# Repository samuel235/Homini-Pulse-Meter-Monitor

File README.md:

# Homini Pulse Meter Monitor

## Brief Description
This ATMEGA328P based board has been created to enable wireless monitoring of your power meter. The product comprises of two parts, one sensor attachment and one custom ATMEGA328P board that the sensor connects to. Both parts are enclosed inside of their own 3D printed enclosures to ensure safety to the devices.

This device has been designed to be located directly on your power meter, the sensor is stuck to the front and the controller is enclosed off to the side of the meter, designed to stick to the side also with Velcro, but you can put it where you wish. The sensor module is attached to the Controller device via a micro USB connector but obviously this can be modified to suit your personal needs.

There is a footprint to allow the use of a AT25DF512C Flash IC to allow the use of OTA updates with MYSBootloader, please refer to the MYSBootloader documentation for the use of this feature to discover the needed fuses and process to install MYSBootloader itself. This enables you the option of updating the device for future software updates without physically getting to the device. We have also allowed the use of a ATSHA204 hardware signing by including a footprint for the ATSHA204 IC on the controller board.

## Function
- To monitor power usage of your home and report back to controller software for a visible display of your consumed electricity.

## Physical Dimensions
- Sensor: 36mm x 24mm x 33mm (Width x Length x Height)
- Controller: TBA

## Connectors
- FTDI and SPI for firmware upgrades
- Micro USB for Powering the device
- Micro USB for sensor connection

## Connections
#### Radio Frequency
Footprints for the following radios will be included.
- nRF24L01 Radio Transceiver
- RFM69 Radio Transceiver

## Power Supply
##### Either of the following:
- Micro USB wall charger.
- CR2450 Coin-cell battery.

## Software
#### Bootloader
- Mains Powered: [Gertsanders' bootloader](https://www.mysensors.org/about/bootloader) running at 16MHz External crystal.
- Battery Powered: [Gertsanders' bootloader](https://www.mysensors.org/about/bootloader) running at 8MHz Internal or External crystal.

If you would like to use OTA updates then please use [MYSBootloader](https://www.mysensors.org/about/ota)

#### Sketch

Will update sketches once I receive PCBs to test different variants of software out:

[Generic pulse sensor sketch Located here](https://www.mysensors.org/build/pulse_power), alternatively you can find customised sketches on my [github](https://github.com/samuel235/Homini-Pulse-Meter-Monitor) inside of the relevant folder to your build type.

## Testing
Testing will commence once boards have been received and assembled.

1. Controller board - Mains powered version - **COMPLETED**
2. Sensor board - Mains powered version - **COMPLETED**

## TO-DO List
1. Add battery monitoring circuitry for next version

## Update Log:
- Micro-Controller board designed (25/03/17)
- Sensor board designed (15/03/17)
- Sensor board (battery) designed (06/04/17)
- All boards ordered using [PCBWay](www.pcbway.com) (10/04/17)
- Board arrived and testing commenced (26/04/17)

## Issues
1. No issues reported at current date.

## Appreciations
Special thanks to:
1. Scalz from the MySensors community that has provided relevant design files and circuit schematics to aid in this product design. [MySensors](https://forum.mysensors.org/user/scalz)/[github](https://github.com/scalz)
2. [Mysensors.org](Mysensors.org)
3. [Openhardware.org](Openhardware.org)
4. [Sparkfun](sparkfun.com) and [Adafruit](adafruit.com) for their parts library for Eagle

If you have any suggestions, please add to the forum post over at [MySensors forum post](https://forum.mysensors.org/topic/6460/homini-pulse-meter-monitor)

I'm very interested in all of your variations, improvements and applications of this module, please add them to the comments with pictures and/or Videos.

## Disclaimer
**_I do not advise you in any way to make/install this product into a property and therefore I take no responsibility for any issues, problems you have or even health implications that you endure while completing the installation or even using the product after installing. BUILD, USE and INSTALL AT YOUR OWN RISK_**

## Licensing
This product is licensed under the CC-BY-SA OpenHardware certificate. For more information please see https://creativecommons.org/licenses/by-sa/4.0/

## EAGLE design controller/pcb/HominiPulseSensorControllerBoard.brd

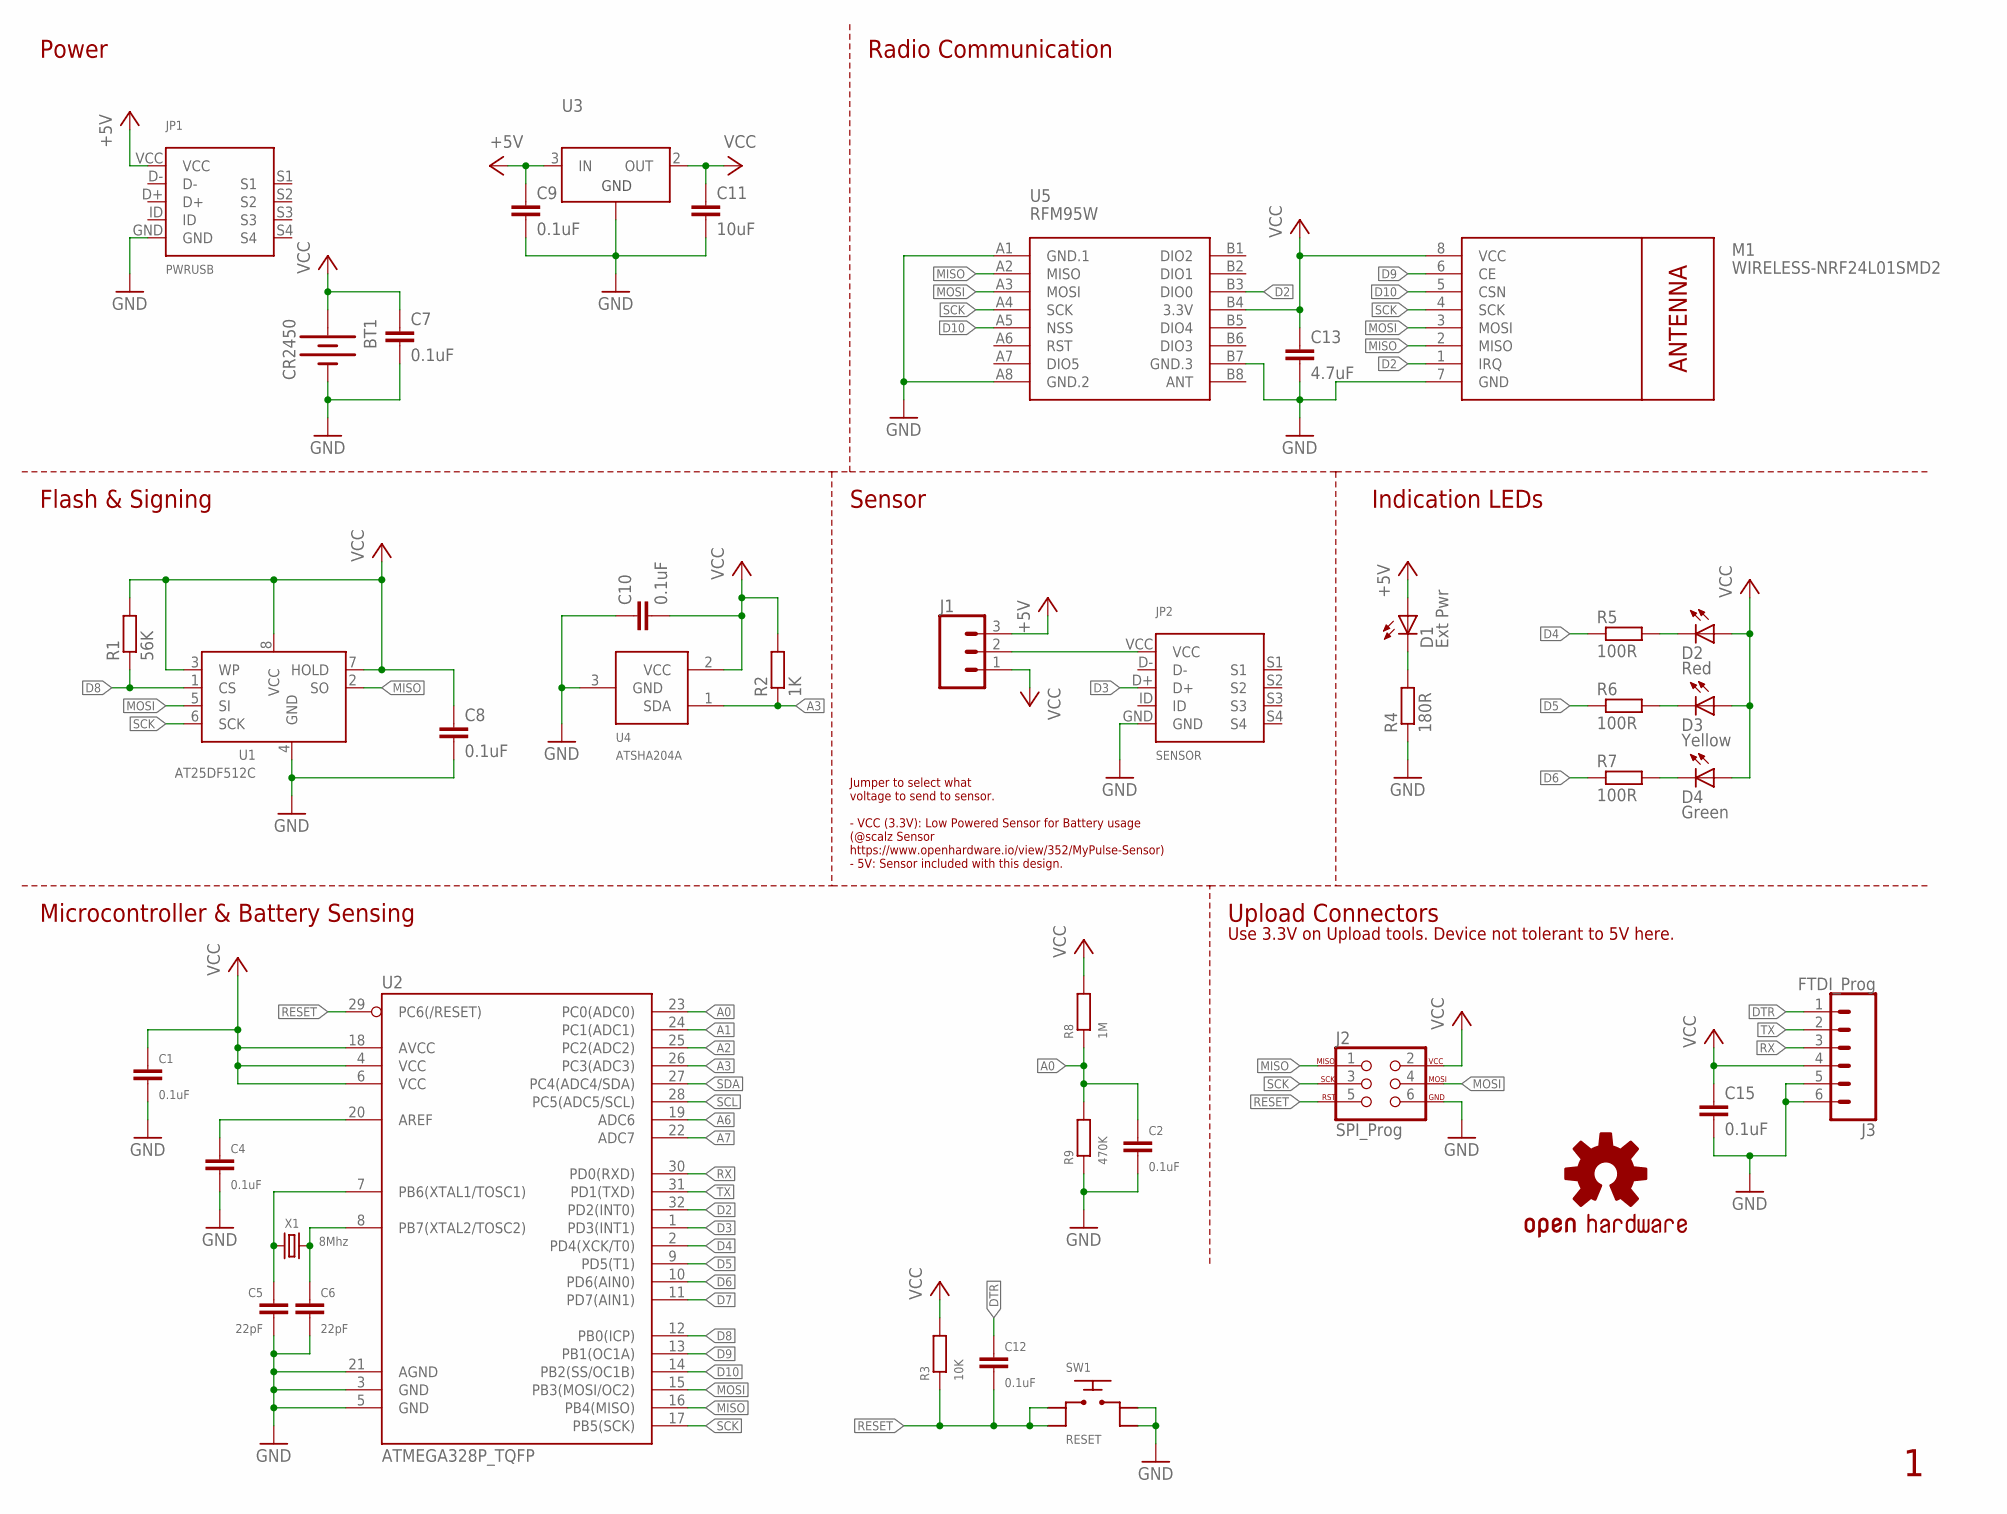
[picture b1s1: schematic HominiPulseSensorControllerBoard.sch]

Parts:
BT1: CR2450; BATTCON_24.5MM
C1, C2, C4, C7, C8, C9, C10, C12, C15: 0.1uF; C0603
C5, C6: 22pF; C0603
C11: 10uF; C0603
C13: 4.7uF; C0603
D1: Ext Pwr; LED3MM
D2: Red; LED3MM
D3: Yellow; LED3MM
D4: Green; LED3MM
J1: CONN_03; 1X03
J2: SPI_Prog; 2X3
J3: FTDI_Prog; 1X06_NO_SILK
JP1: PWRUSB; MICROUSBSMD
JP2: SENSOR; MICROUSBSMD
LOGO1: OSHW-LOGOM; OSHW-LOGO-M
M1: WIRELESS-NRF24L01SMD2; WIRELESS-NRF24L01-SMD-2
R1: 56K; R0603
R2: 1K; R0603
R3: 10K; R0603
R4: 180R; R0603
R5, R6, R7: 100R; R0603
R8: 1M; R0603
R9: 470K; R0603
SW1: RESET; SMD5X5X1.5MM
U1: AT25DF512C; SOIC-8
U2: ATMEGA328P_TQFP; TQFP32-08
U3: LD1117V33; SOC-223
U4: ATSHA204A; SOT23
U5: RFM95W; WIRELESS-LORA-RFM95W#SMD
X1: 8Mhz; HC-49S-SMT

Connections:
+5V: C9.1, D1.A, J1.3, JP1.VCC, U3.3 (IN)
A0: C2.1, R8.1, R9.2, U2.23 (PC0(ADC0))
A1: U2.24 (PC1(ADC1))
A2: U2.25 (PC2(ADC2))
A3: R2.1, U2.26 (PC3(ADC3)), U4.1 (SDA)
A6: U2.19 (ADC6)
A7: U2.22 (ADC7)
D2: M1.1 (IRQ), U2.32 (PD2(INT0)), U5.B3 (DIO0)
D3: JP2.D+, U2.1 (PD3(INT1))
D4: R5.1, U2.2 (PD4(XCK/T0))
D5: R6.1, U2.9 (PD5(T1))
D6: R7.1, U2.10 (PD6(AIN0))
D7: U2.11 (PD7(AIN1))
D8: R1.1, U1.1 (CS), U2.12 (PB0(ICP))
D9: M1.6 (CE), U2.13 (PB1(OC1A))
D10: M1.5 (CSN), U2.14 (PB2(SS/OC1B)), U5.A5 (NSS)
DTR: C12.1, J3.1
GND: BT1.2 (-), C1.2, C2.2, C4.2, C5.2, C6.2, C7.2, C8.2, C9.2, C10.1, C11.2, C13.2, C15.2, J2.6, J3.5, J3.6, JP1.GND, JP2.GND, M1.7 (GND), R4.1, R9.1, SW1.3, SW1.4, U1.4 (GND), U2.3 (GND), U2.5 (GND), U2.21 (AGND), U3.1 (GND), U4.3 (GND), U5.A1 (GND.1), U5.A8 (GND.2), U5.B7 (GND.3)
MISO: J2.1, M1.2 (MISO), U1.2 (SO), U2.16 (PB4(MISO)), U5.A2 (MISO)
MOSI: J2.4, M1.3 (MOSI), U1.5 (SI), U2.15 (PB3(MOSI/OC2)), U5.A3 (MOSI)
unnamed: C6.1, U2.8 (PB7(XTAL2/TOSC2)), X1.1
unnamed: C5.1, U2.7 (PB6(XTAL1/TOSC1)), X1.2
unnamed: C4.1, U2.20 (AREF)
unnamed: J1.2, JP2.VCC
unnamed: D1.K (C), R4.2
unnamed: D2.K (C), R5.2
unnamed: D3.K (C), R6.2
unnamed: D4.K (C), R7.2
RESET: C12.2, J2.5, R3.1, SW1.1, SW1.2, U2.29 (PC6(/RESET))
RX: J3.3, U2.30 (PD0(RXD))
SCK: J2.3, M1.4 (SCK), U1.6 (SCK), U2.17 (PB5(SCK)), U5.A4 (SCK)
SCL: U2.28 (PC5(ADC5/SCL))
SDA: U2.27 (PC4(ADC4/SDA))
TX: J3.2, U2.31 (PD1(TXD))
VCC: BT1.1 (+), C1.1, C7.1, C8.1, C10.2, C11.1, C13.1, C15.1, D2.A, D3.A, D4.A, J1.1, J2.2, J3.4, M1.8 (VCC), R1.2, R2.2, R3.2, R8.2, U1.3 (WP), U1.7 (HOLD), U1.8 (VCC), U2.4 (VCC), U2.6 (VCC), U2.18 (AVCC), U3.2 (OUT), U4.2 (VCC), U5.B4 (3.3V)

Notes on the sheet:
Jumper to select what voltage to send to sensor. - VCC (3.3V): Low Powered Sensor for Battery usage (@scalz Sensor https://www.openhardware.io/view/352/MyPulse-Sensor) - 5V: Sensor included with this design.
Upload Connectors
Microcontroller & Battery Sensing
Power
Flash & Signing
Sensor
Indication LEDs
Radio Communication
Use 3.3V on Upload tools. Device not tolerant to 5V here.

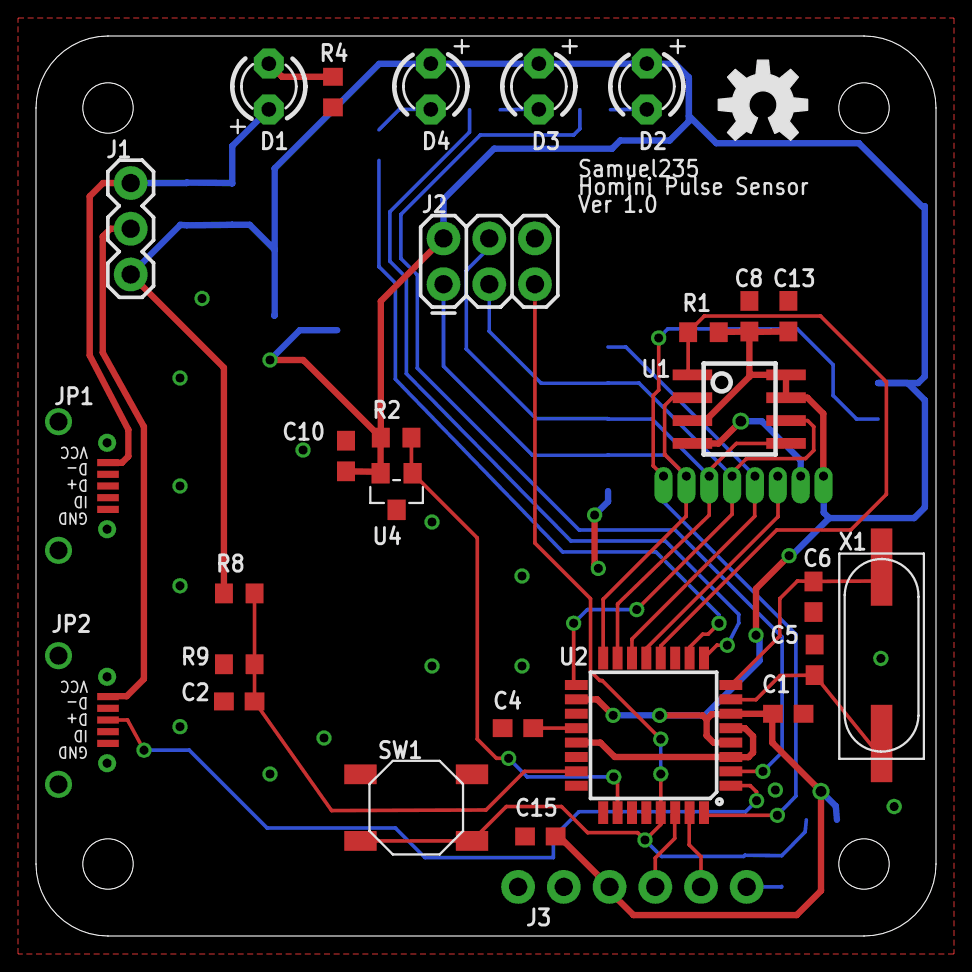
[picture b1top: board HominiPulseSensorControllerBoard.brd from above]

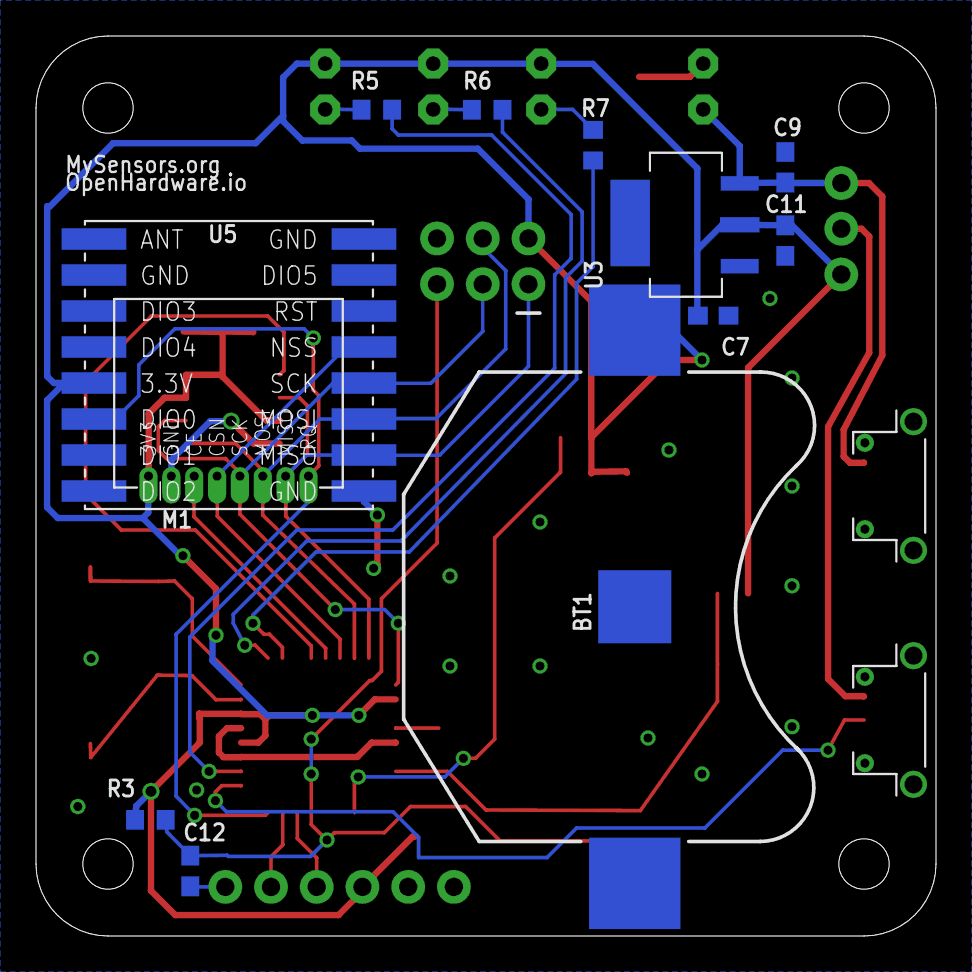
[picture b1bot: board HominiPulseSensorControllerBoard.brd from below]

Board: 2 copper layers, 50.0 x 50.0 mm, 41 parts (12 on the bottom side), 28 nets.

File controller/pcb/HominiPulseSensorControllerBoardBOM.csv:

"Part";"Value";"Device";"Package";"Description";"PROD_ID";"VALUE";
"BT1";"CR2450";"CR2450";"BATTCON_24.5MM";"";"";"";
"C1";"0.1uF";"C-EUC0603";"C0603";"CAPACITOR, European symbol";"";"";
"C2";"0.1uF";"C-EUC0603";"C0603";"CAPACITOR, European symbol";"";"";
"C4";"0.1uF";"C-EUC0603";"C0603";"CAPACITOR, European symbol";"";"";
"C5";"22pF";"C-EUC0603";"C0603";"CAPACITOR, European symbol";"";"";
"C6";"22pF";"C-EUC0603";"C0603";"CAPACITOR, European symbol";"";"";
"C7";"0.1uF";"C-EUC0603";"C0603";"CAPACITOR, European symbol";"";"";
"C8";"0.1uF";"C-EUC0603";"C0603";"CAPACITOR, European symbol";"";"";
"C9";"0.1uF";"C-EUC0603";"C0603";"CAPACITOR, European symbol";"";"";
"C10";"0.1uF";"C-EUC0603";"C0603";"CAPACITOR, European symbol";"";"";
"C11";"10uF";"C-EUC0603";"C0603";"CAPACITOR, European symbol";"";"";
"C12";"0.1uF";"C-EUC0603";"C0603";"CAPACITOR, European symbol";"";"";
"C13";"4.7uF";"C-EUC0603";"C0603";"CAPACITOR, European symbol";"";"";
"C15";"0.1uF";"C-EUC0603";"C0603";"CAPACITOR, European symbol";"";"";
"D1";"Ext Pwr";"LED3MM";"LED3MM";"LED";"";"";
"D2";"Red";"LED3MM";"LED3MM";"LED";"";"";
"D3";"Yellow";"LED3MM";"LED3MM";"LED";"";"";
"D4";"Green";"LED3MM";"LED3MM";"LED";"";"";
"J1";"";"CONN_03";"1X03";"Multi connection point. Often used as Generic Header-pin footprint for 0.1 inch spaced/style header connections";"";"";
"J2";"SPI_Prog";"AVR_SPI_PROG_3X2PTH";"2X3";"AVR ISP 6 Pin";"";"";
"J3";"FTDI_Prog";"CONN_06NO_SILK_FEMALE_PTH";"1X06_NO_SILK";"Multi connection point. Often used as Generic Header-pin footprint for 0.1 inch spaced/style header connections";"CONN-08437";"";
"JP1";"PWRUSB";"MICROUSBSMD";"MICROUSBSMD";"";"";"";
"JP2";"SENSOR";"MICROUSBSMD";"MICROUSBSMD";"";"";"";
"M1";"WIRELESS-NRF24L01SMD2";"WIRELESS-NRF24L01SMD2";"WIRELESS-NRF24L01-SMD-2";"2.4 GHz Wireless Module based on NRF24L01 chip";"";"";
"R1";"56K";"R-EU_R0603";"R0603";"RESISTOR, European symbol";"";"";
"R2";"1K";"R-EU_R0603";"R0603";"RESISTOR, European symbol";"";"";
"R3";"10K";"R-EU_R0603";"R0603";"RESISTOR, European symbol";"";"";
"R4";"180R";"R-EU_R0603";"R0603";"RESISTOR, European symbol";"";"";
"R5";"100R";"R-EU_R0603";"R0603";"RESISTOR, European symbol";"";"";
"R6";"100R";"R-EU_R0603";"R0603";"RESISTOR, European symbol";"";"";
"R7";"100R";"R-EU_R0603";"R0603";"RESISTOR, European symbol";"";"";
"R8";"1M";"R-EU_R0603";"R0603";"RESISTOR, European symbol";"";"";
"R9";"470K";"R-EU_R0603";"R0603";"RESISTOR, European symbol";"";"";
"SW1";"RESET";"SMD5X5X1.5MM";"SMD5X5X1.5MM";"";"";"";
"U1";"AT25DF512C";"AT25DF512C";"SOIC-8";"";"";"";
"U2";"ATMEGA328P_TQFP";"ATMEGA328P_TQFP";"TQFP32-08";"Popular 328P in QFP";"IC-09069";"ATMEGA328P_TQFP";
"U3";"";"LD1117V33";"SOC-223";"";"";"";
"U4";"ATSHA204A";"ATSHA204A";"SOT23";"";"";"";
"U5";"RFM95W";"WIRELESS-LORA-RFM95W#SMD";"WIRELESS-LORA-RFM95W#SMD";"868/915 MHz LoRa Radio Transceiver Module based on SX1276 chip";"";"";
"X1";"8Mhz";"HC-49S-SMT";"HC-49S-SMT";"";"";"";

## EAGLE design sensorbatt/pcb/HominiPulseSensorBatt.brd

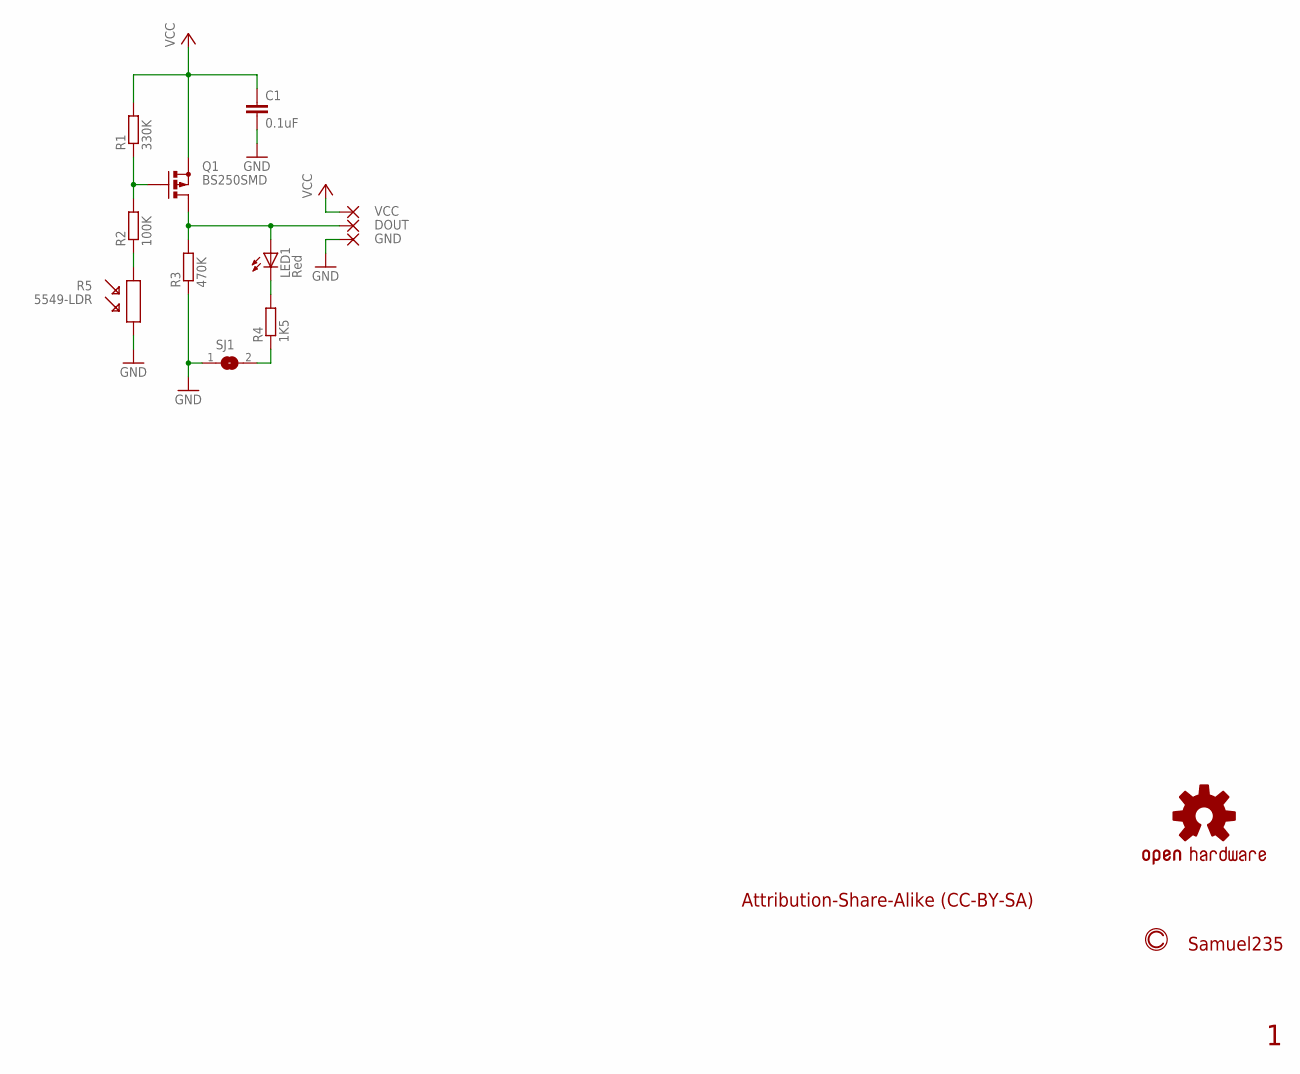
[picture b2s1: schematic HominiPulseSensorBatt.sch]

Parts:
C1: 0.1uF; C0603
DOUT: SMD2; SMD1,27-2,54
GND: SMD2; SMD1,27-2,54
LED1: Red; LED3MM
LOGO1: OSHW-LOGOS; OSHW-LOGO-S
Q1: BS250SMD; SOT23
R1: 330K; R0603
R2: 100K; R0603
R3: 470K; R0603
R4: 1K5; R0603
R5: 5549-LDR; LDR-PTH
SJ1: SJ
VCC: SMD2; SMD1,27-2,54

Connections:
GND: C1.2, GND.1, R3.1, R5.1, SJ1.1
unnamed: Q1.1 (G), R1.1, R2.2
unnamed: R2.1, R5.2
unnamed: DOUT.1, LED1.A, Q1.3 (D), R3.2
unnamed: R4.1, SJ1.2
unnamed: LED1.K (C), R4.2
VCC: C1.1, Q1.2 (S), R1.2, VCC.1

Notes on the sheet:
Samuel235
Attribution-Share-Alike (CC-BY-SA)

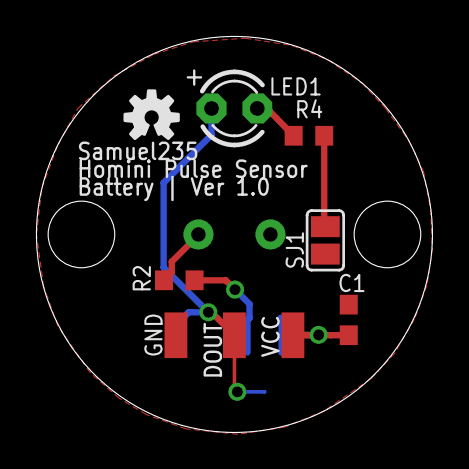
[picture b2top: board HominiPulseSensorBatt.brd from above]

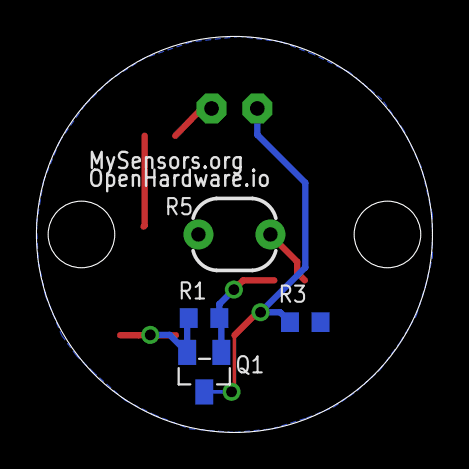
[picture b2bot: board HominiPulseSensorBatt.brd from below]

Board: 2 copper layers, 22.0 x 22.0 mm, 13 parts (4 on the bottom side), 7 nets.

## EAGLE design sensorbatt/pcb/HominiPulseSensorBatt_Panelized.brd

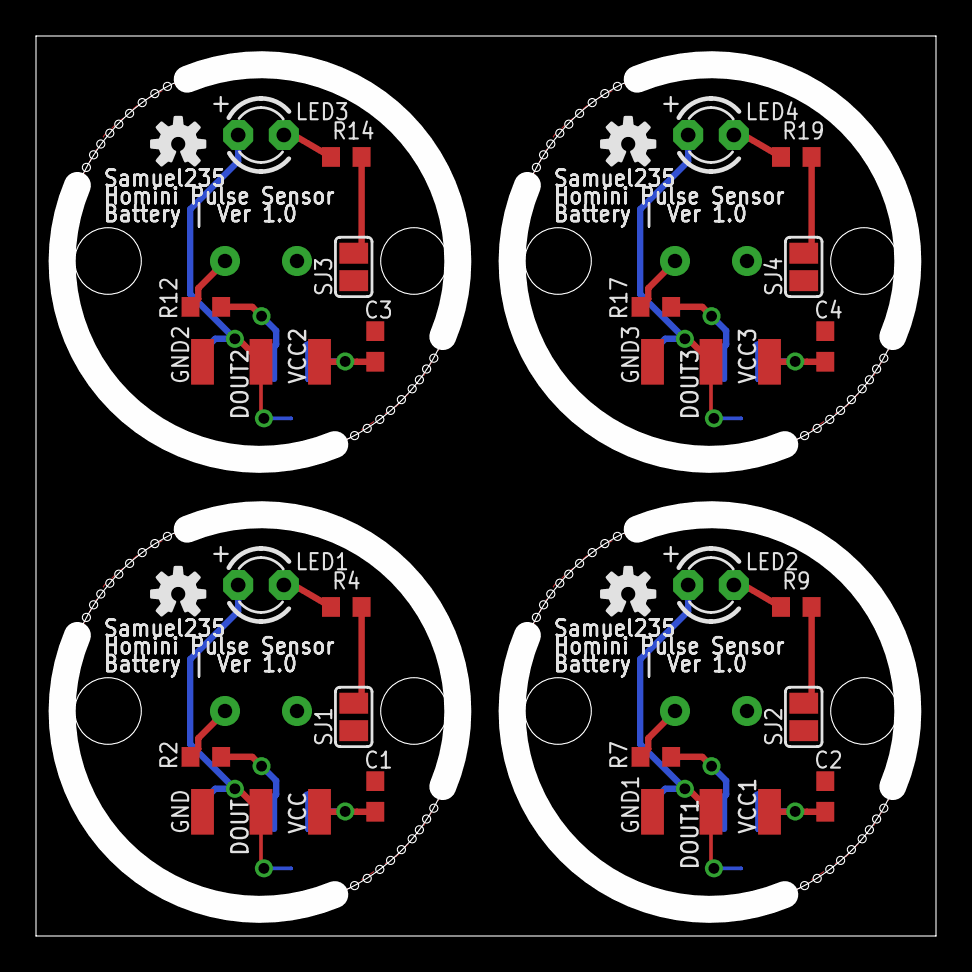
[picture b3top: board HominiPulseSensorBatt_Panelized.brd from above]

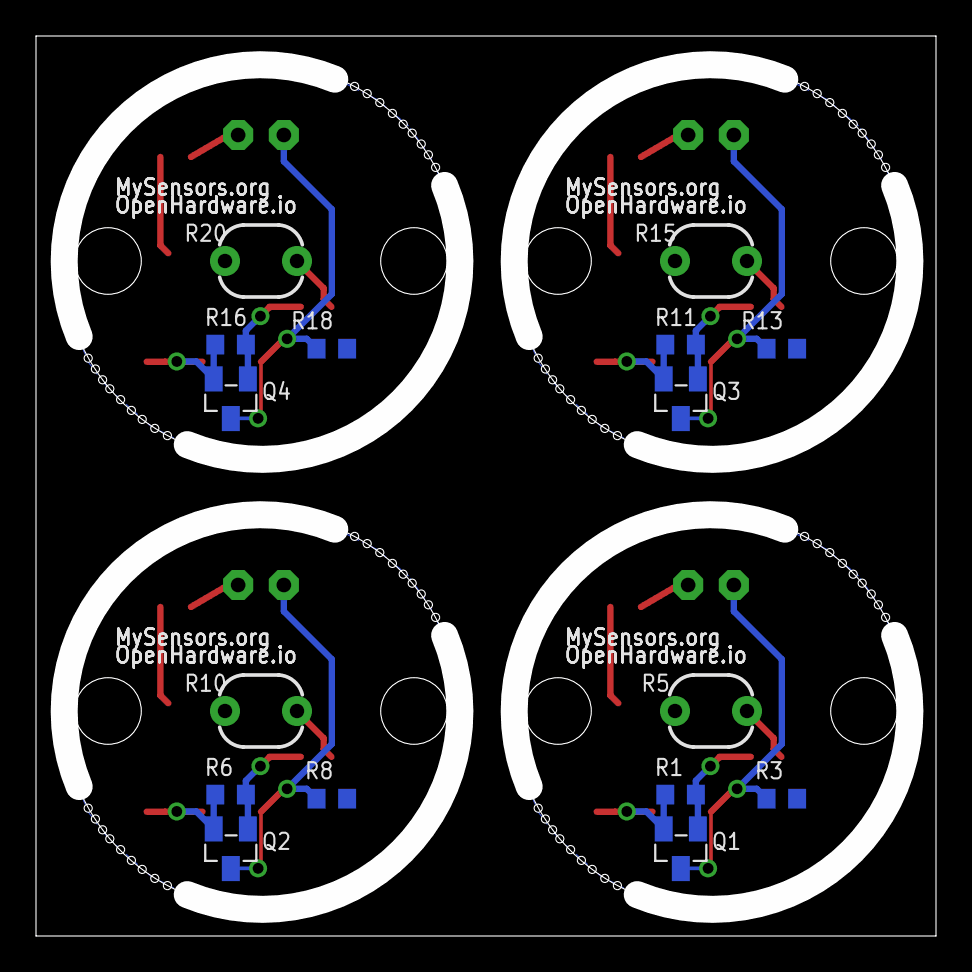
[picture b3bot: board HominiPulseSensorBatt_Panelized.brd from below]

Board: 2 copper layers, 48.5 x 48.5 mm, 52 parts (16 on the bottom side), 28 nets.

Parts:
C1, C2, C3, C4: 0.1uF; C0603
DOUT, DOUT1, DOUT2, DOUT3: SMD1,27-2,54
GND, GND1, GND2, GND3: SMD1,27-2,54
LED1, LED2, LED3, LED4: Red; LED3MM
LOGO1, LOGO2, LOGO3, LOGO4: OSHW-LOGOS; OSHW-LOGO-S
Q1, Q2, Q3, Q4: BS250SMD; SOT23
R1, R6, R11, R16: 330K; R0603
R2, R7, R12, R17: 100K; R0603
R3, R8, R13, R18: 470K; R0603
R4, R9, R14, R19: 1K5; R0603
R5, R10, R15, R20: 5549-LDR; LDR-PTH
SJ1, SJ2, SJ3, SJ4: SJ
VCC, VCC1, VCC2, VCC3: SMD1,27-2,54

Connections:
GND: C1.2, GND.1, R3.1, R5.1, SJ1.1
GND1: C2.2, GND1.1, R8.1, R10.1, SJ2.1
GND2: C3.2, GND2.1, R13.1, R15.1, SJ3.1
GND3: C4.2, GND3.1, R18.1, R20.1, SJ4.1
unnamed: Q1.1, R1.1, R2.2
unnamed: R2.1, R5.2
unnamed: DOUT.1, LED1.A, Q1.3, R3.2
unnamed: R4.1, SJ1.2
unnamed: LED1.K, R4.2
unnamed: Q2.1, R6.1, R7.2
unnamed: R7.1, R10.2
unnamed: DOUT1.1, LED2.A, Q2.3, R8.2
unnamed: R9.1, SJ2.2
unnamed: LED2.K, R9.2
unnamed: Q3.1, R11.1, R12.2
unnamed: R12.1, R15.2
unnamed: DOUT2.1, LED3.A, Q3.3, R13.2
unnamed: R14.1, SJ3.2
unnamed: LED3.K, R14.2
unnamed: Q4.1, R16.1, R17.2
unnamed: R17.1, R20.2
unnamed: DOUT3.1, LED4.A, Q4.3, R18.2
unnamed: R19.1, SJ4.2
unnamed: LED4.K, R19.2
VCC: C1.1, Q1.2, R1.2, VCC.1
VCC1: C2.1, Q2.2, R6.2, VCC1.1
VCC2: C3.1, Q3.2, R11.2, VCC2.1
VCC3: C4.1, Q4.2, R16.2, VCC3.1

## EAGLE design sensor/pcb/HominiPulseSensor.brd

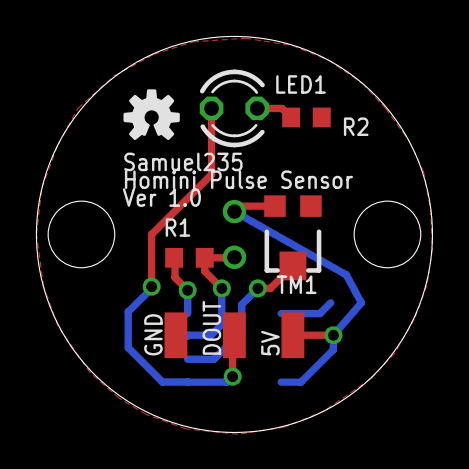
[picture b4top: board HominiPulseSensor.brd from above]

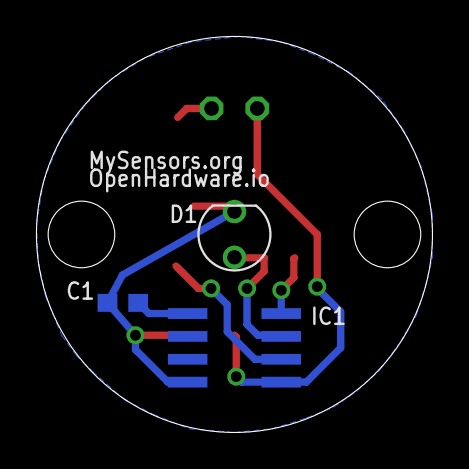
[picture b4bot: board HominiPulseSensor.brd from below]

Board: 2 copper layers, 22.0 x 22.0 mm, 11 parts (3 on the bottom side), 6 nets.

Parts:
5V: SMD1,27-2,54
C1: 0.1uF; C0603
D1: PD204-6C; 3MM-PTH
DOUT: SMD1,27-2,54
GND: SMD1,27-2,54
IC1: LM393D; SO08
LED1: Red; LED3MM
LOGO1: OSHW-LOGOS; OSHW-LOGO-S
R1: 33k; R0603
R2: 180R; R0603
TM1: 10k; TC33X

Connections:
+5V: 5V.1, C1.1, D1.C, IC1.8, TM1.3
GND: C1.2, GND.1, IC1.4, IC1.5, IC1.6, R1.1, R2.1, TM1.1
unnamed: D1.A, IC1.3, R1.2
unnamed: IC1.2, TM1.2
unnamed: DOUT.1, IC1.1, LED1.A
unnamed: LED1.K, R2.2

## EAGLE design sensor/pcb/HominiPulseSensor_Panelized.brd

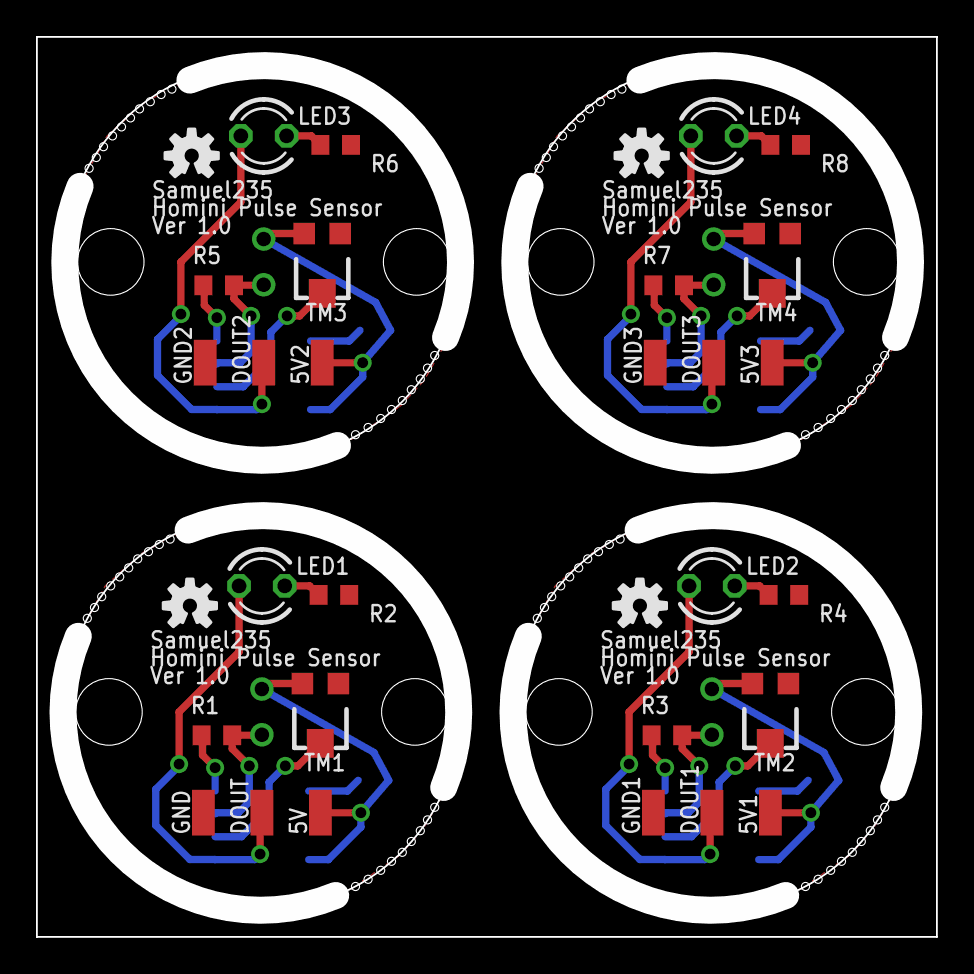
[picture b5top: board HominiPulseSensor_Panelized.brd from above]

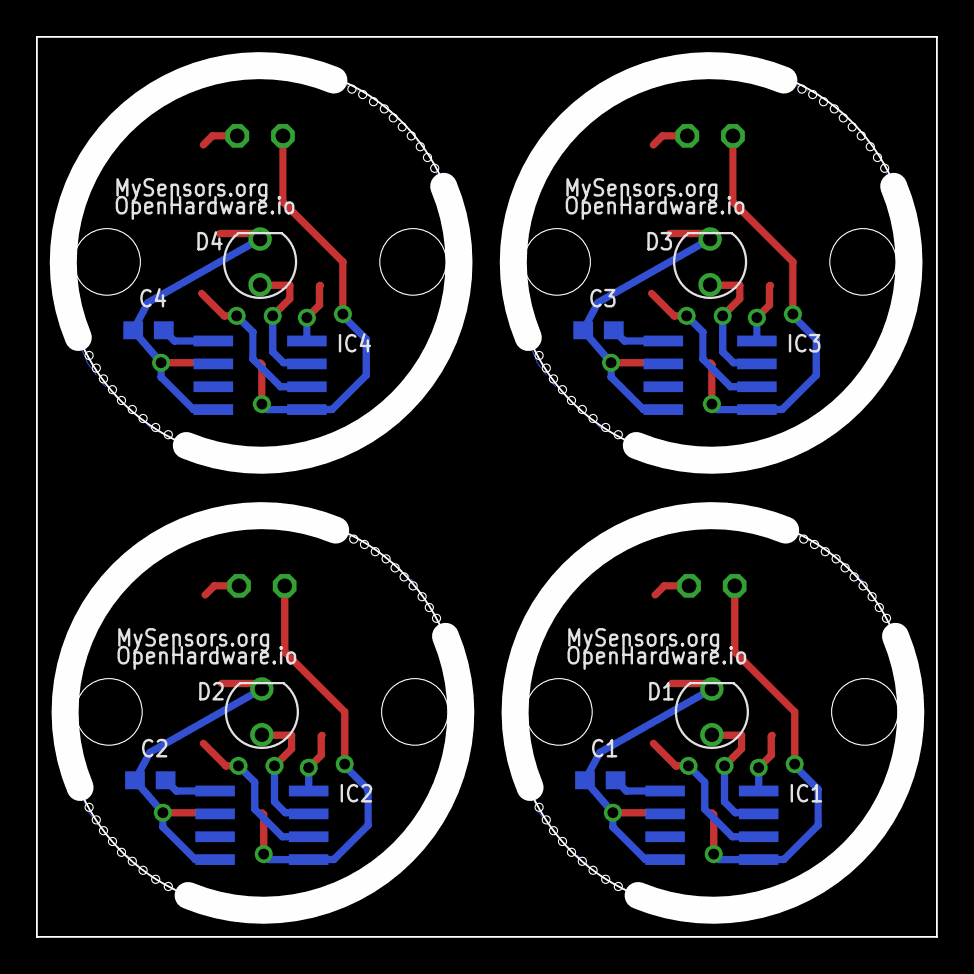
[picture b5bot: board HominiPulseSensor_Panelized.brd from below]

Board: 2 copper layers, 48.6 x 48.6 mm, 44 parts (12 on the bottom side), 24 nets.

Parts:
5V, 5V1, 5V2, 5V3: SMD1,27-2,54
C1, C2, C3, C4: 0.1uF; C0603
D1, D2, D3, D4: PD204-6C; 3MM-PTH
DOUT, DOUT1, DOUT2, DOUT3: SMD1,27-2,54
GND, GND1, GND2, GND3: SMD1,27-2,54
IC1, IC2, IC3, IC4: LM393D; SO08
LED1, LED2, LED3, LED4: Red; LED3MM
LOGO1, LOGO2, LOGO3, LOGO4: OSHW-LOGOS; OSHW-LOGO-S
R1, R3, R5, R7: 33k; R0603
R2, R4, R6, R8: 180R; R0603
TM1, TM2, TM3, TM4: 10k; TC33X

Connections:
+5V: 5V.1, C1.1, D1.C, IC1.8, TM1.3
+5V1: 5V1.1, C2.1, D2.C, IC2.8, TM2.3
+5V2: 5V2.1, C3.1, D3.C, IC3.8, TM3.3
+5V3: 5V3.1, C4.1, D4.C, IC4.8, TM4.3
GND: C1.2, GND.1, IC1.4, IC1.5, IC1.6, R1.1, R2.1, TM1.1
GND1: C2.2, GND1.1, IC2.4, IC2.5, IC2.6, R3.1, R4.1, TM2.1
GND2: C3.2, GND2.1, IC3.4, IC3.5, IC3.6, R5.1, R6.1, TM3.1
GND3: C4.2, GND3.1, IC4.4, IC4.5, IC4.6, R7.1, R8.1, TM4.1
unnamed: D1.A, IC1.3, R1.2
unnamed: IC1.2, TM1.2
unnamed: D2.A, IC2.3, R3.2
unnamed: DOUT.1, IC1.1, LED1.A
unnamed: LED1.K, R2.2
unnamed: DOUT1.1, IC2.1, LED2.A
unnamed: LED2.K, R4.2
unnamed: IC2.2, TM2.2
unnamed: D3.A, IC3.3, R5.2
unnamed: DOUT2.1, IC3.1, LED3.A
unnamed: LED3.K, R6.2
unnamed: IC3.2, TM3.2
unnamed: D4.A, IC4.3, R7.2
unnamed: DOUT3.1, IC4.1, LED4.A
unnamed: LED4.K, R8.2
unnamed: IC4.2, TM4.2

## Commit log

2017-03-25 Update README.md
    Updated some information regarding battery powered devices
2017-03-25 Removal of SketchUp File inside of renders directory
2017-03-25 Improved Folder Structure
    Created new folder structure for better navigation
2017-04-05 Added files
    Added battery sensor files
    Added datasheets for controller board
    Removed gerber zip file - Individual files remain in git
2017-04-06 Added Files
    Controller gerber & BOM files
    Sensor BOM files
    Sensorbatt BOM files and PCB images
2017-04-10 Files added
    Added some gerbers
    Modified existing gerbers
2017-04-10 Sketchup files added
2017-04-11 Files added
    Solidworks file - Enclosure
    Enclosure render images
2017-04-11 File Update
    Solidworks File - Controller
2017-05-08 Additional files & updates
    Modified some controller CAD files
    Added some controller STL files
    Modified some sensor CAD files
    Added some sensor STL files
    Modified some sensor battery version CAD files
    Added some sensor battery version STL files
2017-05-08 Readme Changes
    Modified README.md

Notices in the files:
parts and their libraries:
SparkFun-Connectors: Licensing: Creative Commons ShareAlike 4.0 International - https://creativecommons.org/licenses/by-sa/4.0
diy-modules: Released under the Creative Commons Attribution 4.0 International License: http://creativecommons.org/licenses/by/4.0
